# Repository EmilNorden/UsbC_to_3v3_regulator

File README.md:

KiCad design for a PCB that takes USB C power input and outputs a steady 3.3v

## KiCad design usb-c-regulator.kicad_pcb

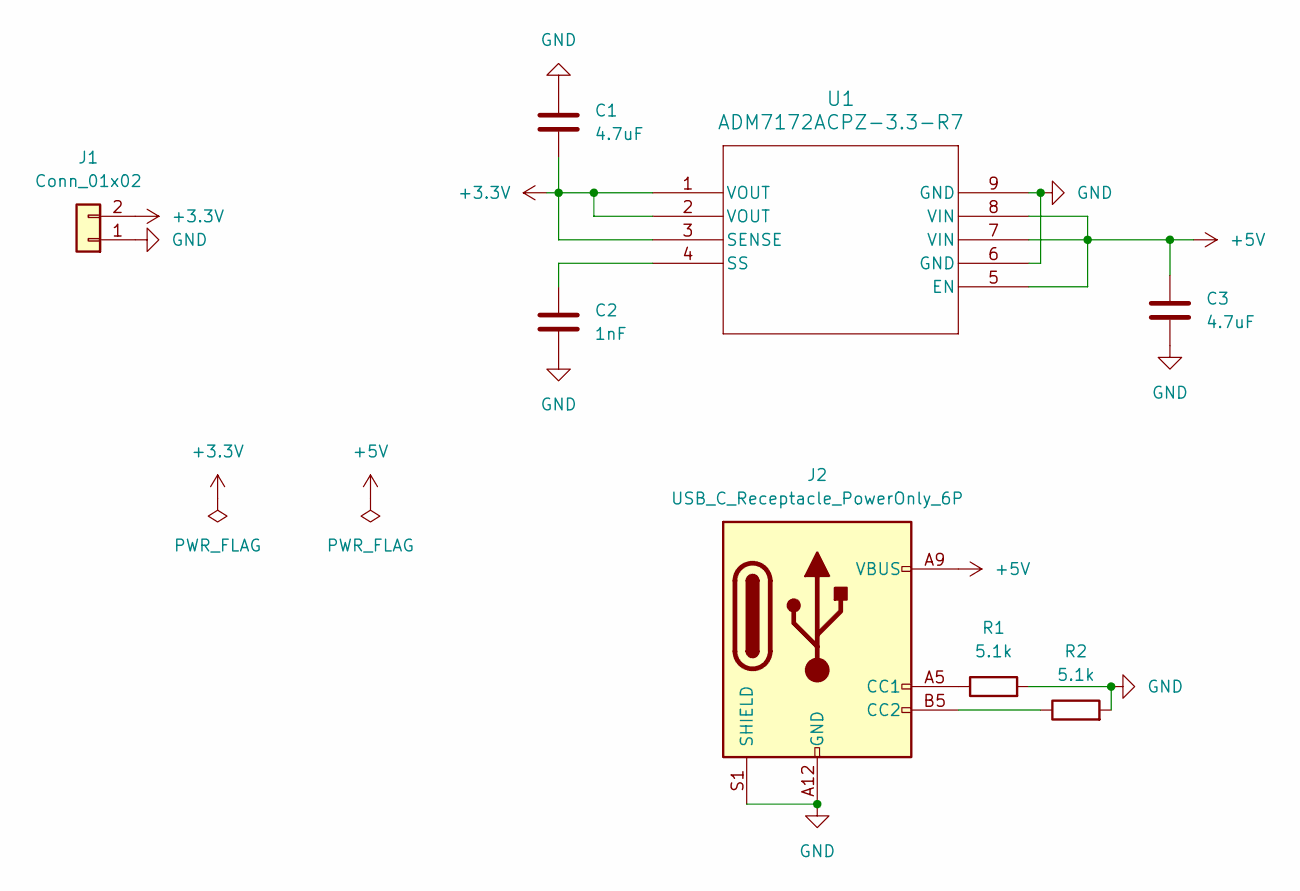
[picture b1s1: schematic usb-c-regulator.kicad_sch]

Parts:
C1, C3: 4.7uF; C_0603_1608Metric
C2: 1nF; C_0603_1608Metric
J1: Conn_01x02; PinHeader_1x02_P2.54mm_Vertical
J2: USB_C_Receptacle_PowerOnly_6P; MC-301D USB Type C Female Connector
R1, R2: 5.1k; R_0805_2012Metric
U1: ADM7172ACPZ-3.3-R7; CP-8-21_ADI

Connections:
+3.3V: C1.2, J1.2, U1.1 (VOUT), U1.2 (VOUT), U1.3 (SENSE)
+5V: C3.1, J2.A9 (VBUS), J2.B9 (VBUS), U1.5 (EN), U1.7 (VIN), U1.8 (VIN)
GND: C1.1, C2.2, C3.2, J1.1, J2.A12 (GND), J2.B12 (GND), J2.S1 (SHIELD), R1.2, R2.2, U1.6 (GND), U1.9 (GND)
unnamed: J2.A5 (CC1), R1.1
unnamed: J2.B5 (CC2), R2.1
unnamed: C2.1, U1.4 (SS)

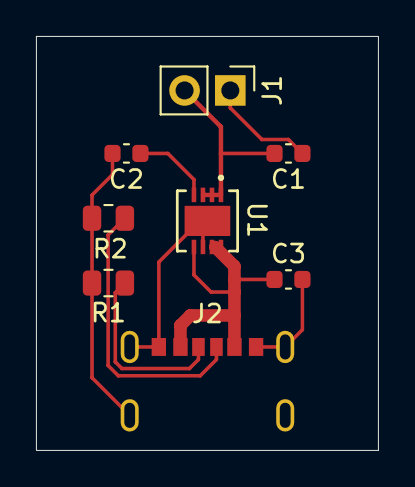
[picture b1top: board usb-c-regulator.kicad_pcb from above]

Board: 2 copper layers, 19.0 x 23.0 mm, 8 parts (0 on the bottom side), 6 nets.

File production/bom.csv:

Designator,Footprint,Quantity,Value,LCSC Part #
"C1, C3",0603,2,4.7uF,C19666 
C2,0603,1,1nF,C1588 
J1,PinHeader_1x02_P2.54mm_Vertical,1,Conn_01x02,C492401 
J2,MC-301D USB Type C Female Connector,1,USB_C_Receptacle_PowerOnly_6P,C283540
"R1, R2",0805,2,5.1k,C27834
U1,LFCSP-8,1,ADM7172ACPZ-3.3-R7,C514342

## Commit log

2025-01-04 adjusted clearance of pad 9 on ADM7172 footprint
2025-01-05 production files
